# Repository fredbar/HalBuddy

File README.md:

# HalBuddy

This project is a rapsberry-based internet enabled button for multiple purpose.

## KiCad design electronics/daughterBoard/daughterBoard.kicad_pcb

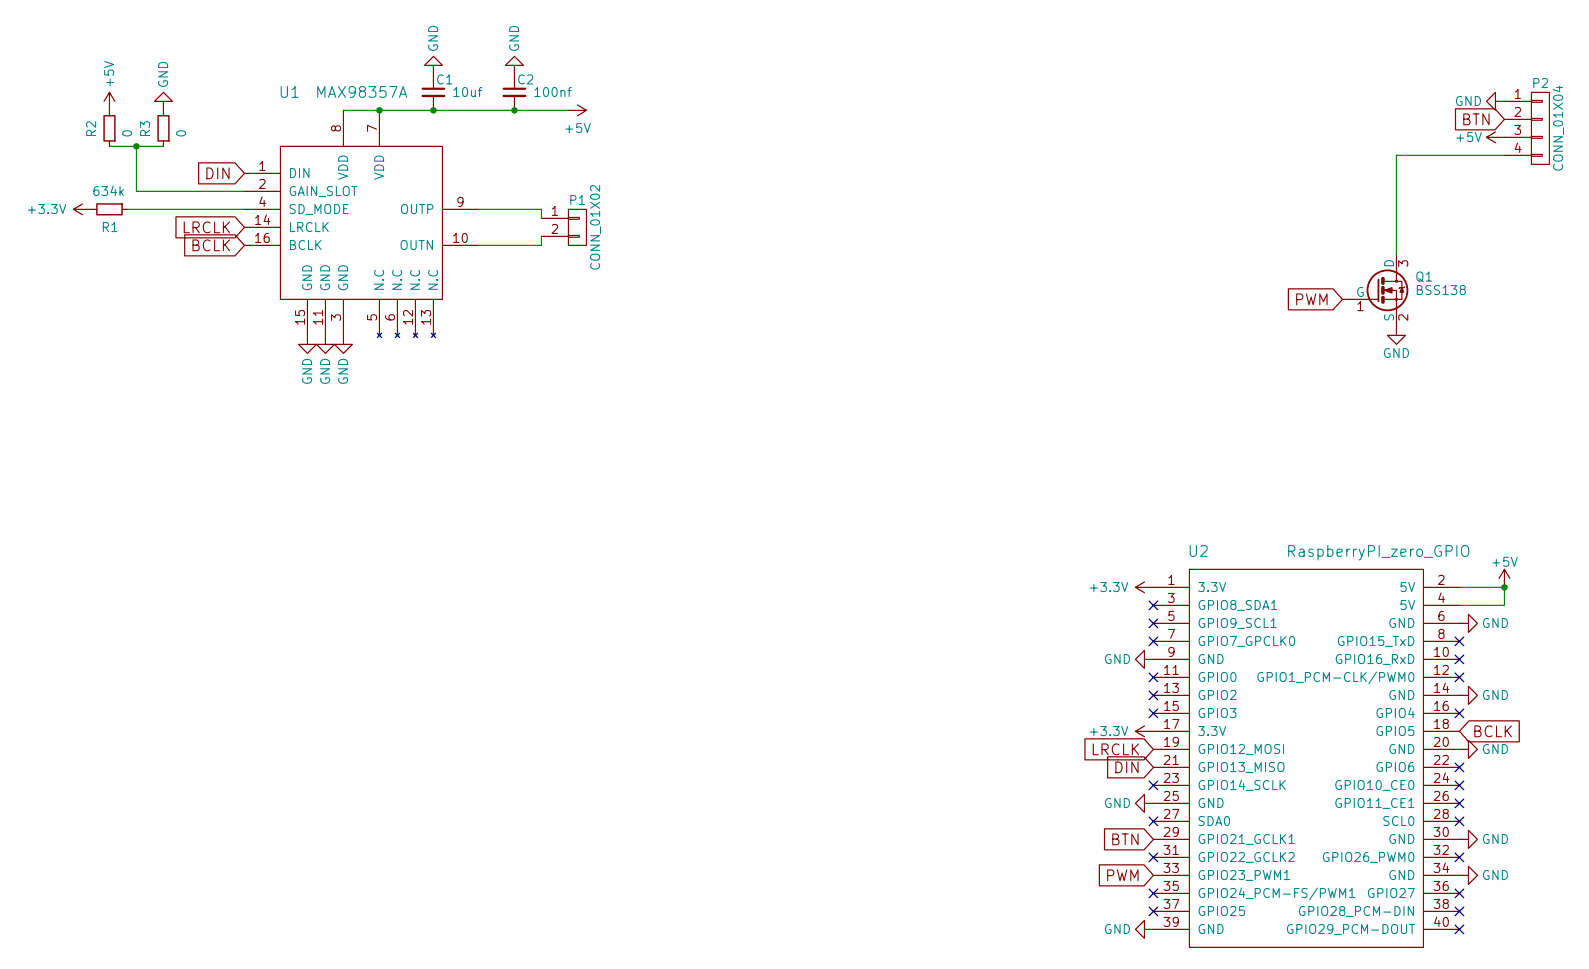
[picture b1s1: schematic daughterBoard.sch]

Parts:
C1: 10uf; C_0603
C2: 100nf; C_0603
P1: CONN_01X02; Pin_Header_Straight_1x02
P2: CONN_01X04; Pin_Header_Angled_1x04
Q1: BSS138; SOT-23
R1: 634k; R_0603
R2, R3: 0; R_0603
U1: MAX98357A; QFN-16-1EP_3x3mm_Pitch0.5mm
U2: RaspberryPI_zero_GPIO; Pin_Header_Straight_2x20

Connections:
+3V3: R1.2, U2.1 (3.3V), U2.17 (3.3V)
+5V: C1.2, C2.2, P2.3, R2.2, U1.7 (VDD), U1.8 (VDD), U2.2 (5V), U2.4 (5V)
BCLK: U1.16 (BCLK), U2.18 (GPIO5)
BTN: P2.2, U2.29 (GPIO21_GCLK1)
DIN: U1.1 (DIN), U2.21 (GPIO13_MISO)
GND: C1.1, C2.1, P2.1, Q1.2 (S), R3.2, U1.3 (GND), U1.11 (GND), U1.15 (GND), U2.6 (GND), U2.9 (GND), U2.14 (GND), U2.20 (GND), U2.25 (GND), U2.30 (GND), U2.34 (GND), U2.39 (GND)
LRCLK: U1.14 (LRCLK), U2.19 (GPIO12_MOSI)
unnamed: P1.1, U1.9 (OUTP)
unnamed: P1.2, U1.10 (OUTN)
unnamed: P2.4, Q1.3 (D)
unnamed: R1.1, U1.4 (SD_MODE)
unnamed: R2.1, R3.1, U1.2 (GAIN_SLOT)
PWM: Q1.1 (G), U2.33 (GPIO23_PWM1)

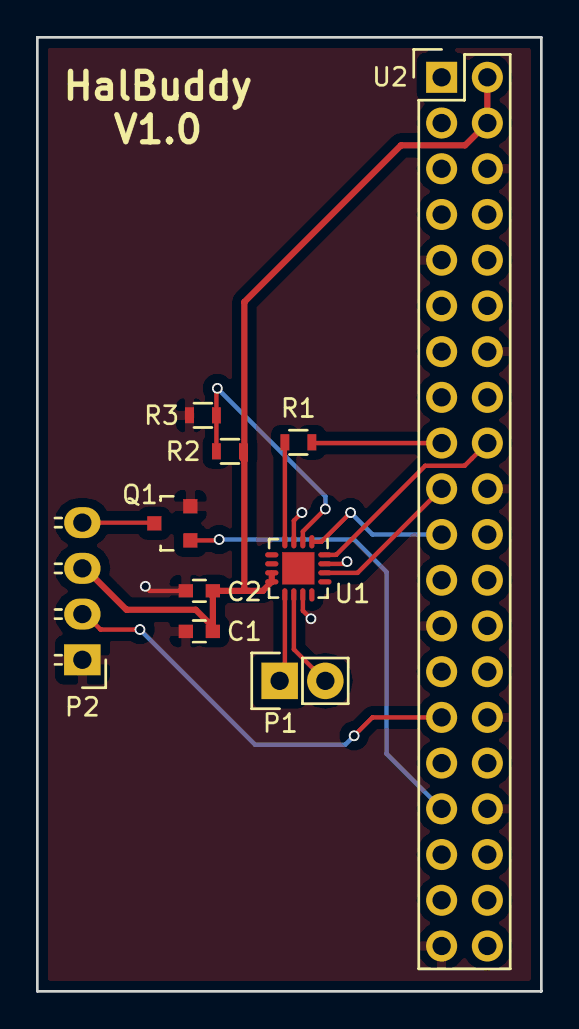
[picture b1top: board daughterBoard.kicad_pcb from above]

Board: 2 copper layers, 28.0 x 53.0 mm, 10 parts (0 on the bottom side), 13 nets.

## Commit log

2017-04-14 first commit. test.
2017-04-17 First version of the daughter board.
    Includes sound and mosfet for driving the LED at 5V.
2017-06-03 Added daughterboard PCB
    Added V1 of the pcb with sound support. Not tested yet, boards are
    still on their way from Shenzen2u.
2017-06-03 Added V1 of the box support
    Not complete and not tested as PCBs are not there.
    Also, waiting for the complete stuff to integrate the speaker grill and
    support.
    Mechanics are done under freeCad: https://www.freecadweb.org
2017-06-03 Added software
    Does not take care of the sound.
    Implements a dummy behavior.
    Still has a bug that needs to be fixed:
    https://github.com/fredbar/HalBuddy/issues/7
    This is a big WIP.
